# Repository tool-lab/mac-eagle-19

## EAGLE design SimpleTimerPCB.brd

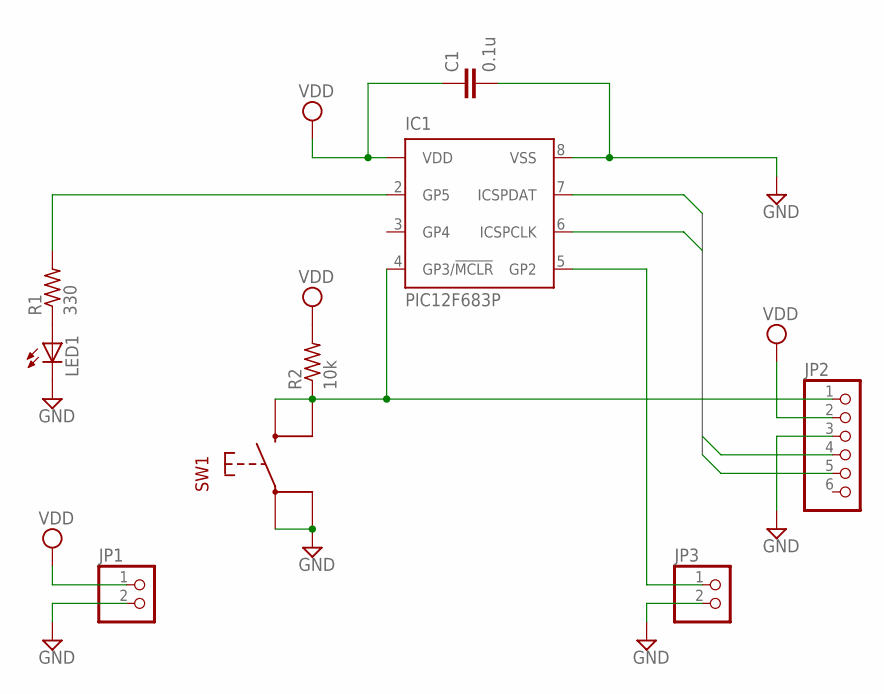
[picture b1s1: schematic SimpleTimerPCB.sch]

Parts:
C1: 0.1u; C050-024X044
IC1: PIC12F683P; DIL8
JP1, JP3: PINHD-1X2; 1X02
JP2: PINHD-1X6; 1X06
LED1: LED3MM
R1: 330; 0204/7
R2: 10k; 0204/7
SW1: TACT-SWITCH; TACTSW-25X20

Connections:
GND: C1.2, IC1.8 (VSS), JP1.2, JP2.3, JP3.2, LED1.K (C), SW1.3 (P1), SW1.4 (P2)
unnamed: LED1.A, R1.1
unnamed: IC1.4 (GP3/!MCLR!), JP2.1, R2.1, SW1.1 (S1), SW1.2 (S2)
unnamed: IC1.2 (GP5), R1.2
unnamed: IC1.5 (GP2), JP3.1
PIN4: IC1.7 (ICSPDAT), JP2.4
PIN5: IC1.6 (ICSPCLK), JP2.5
VDD: C1.1, IC1.1 (VDD), JP1.1, JP2.2, R2.2

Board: 2 copper layers, 9 parts (0 on the bottom side), 8 nets, no tracks yet.
